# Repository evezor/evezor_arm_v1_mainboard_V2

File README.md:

# evezor_arm_v1_mainboard_V2

This is the second iteration of the mainboard. The first version can be found here: https://github.com/evezor/evezor_arm_v1_mainboard_V1

This board retains the Molex KK connectors for the stepper motors and the gadgeteer ports for expansion. 

This version also incorportates a stepdown voltage converter, a power relay and a pair of USB-A ports inteded for powering a raspberry pi and a screen. 

Source files can be found here: https://github.com/evezor/evezor_arm_v1_mainboard_V2

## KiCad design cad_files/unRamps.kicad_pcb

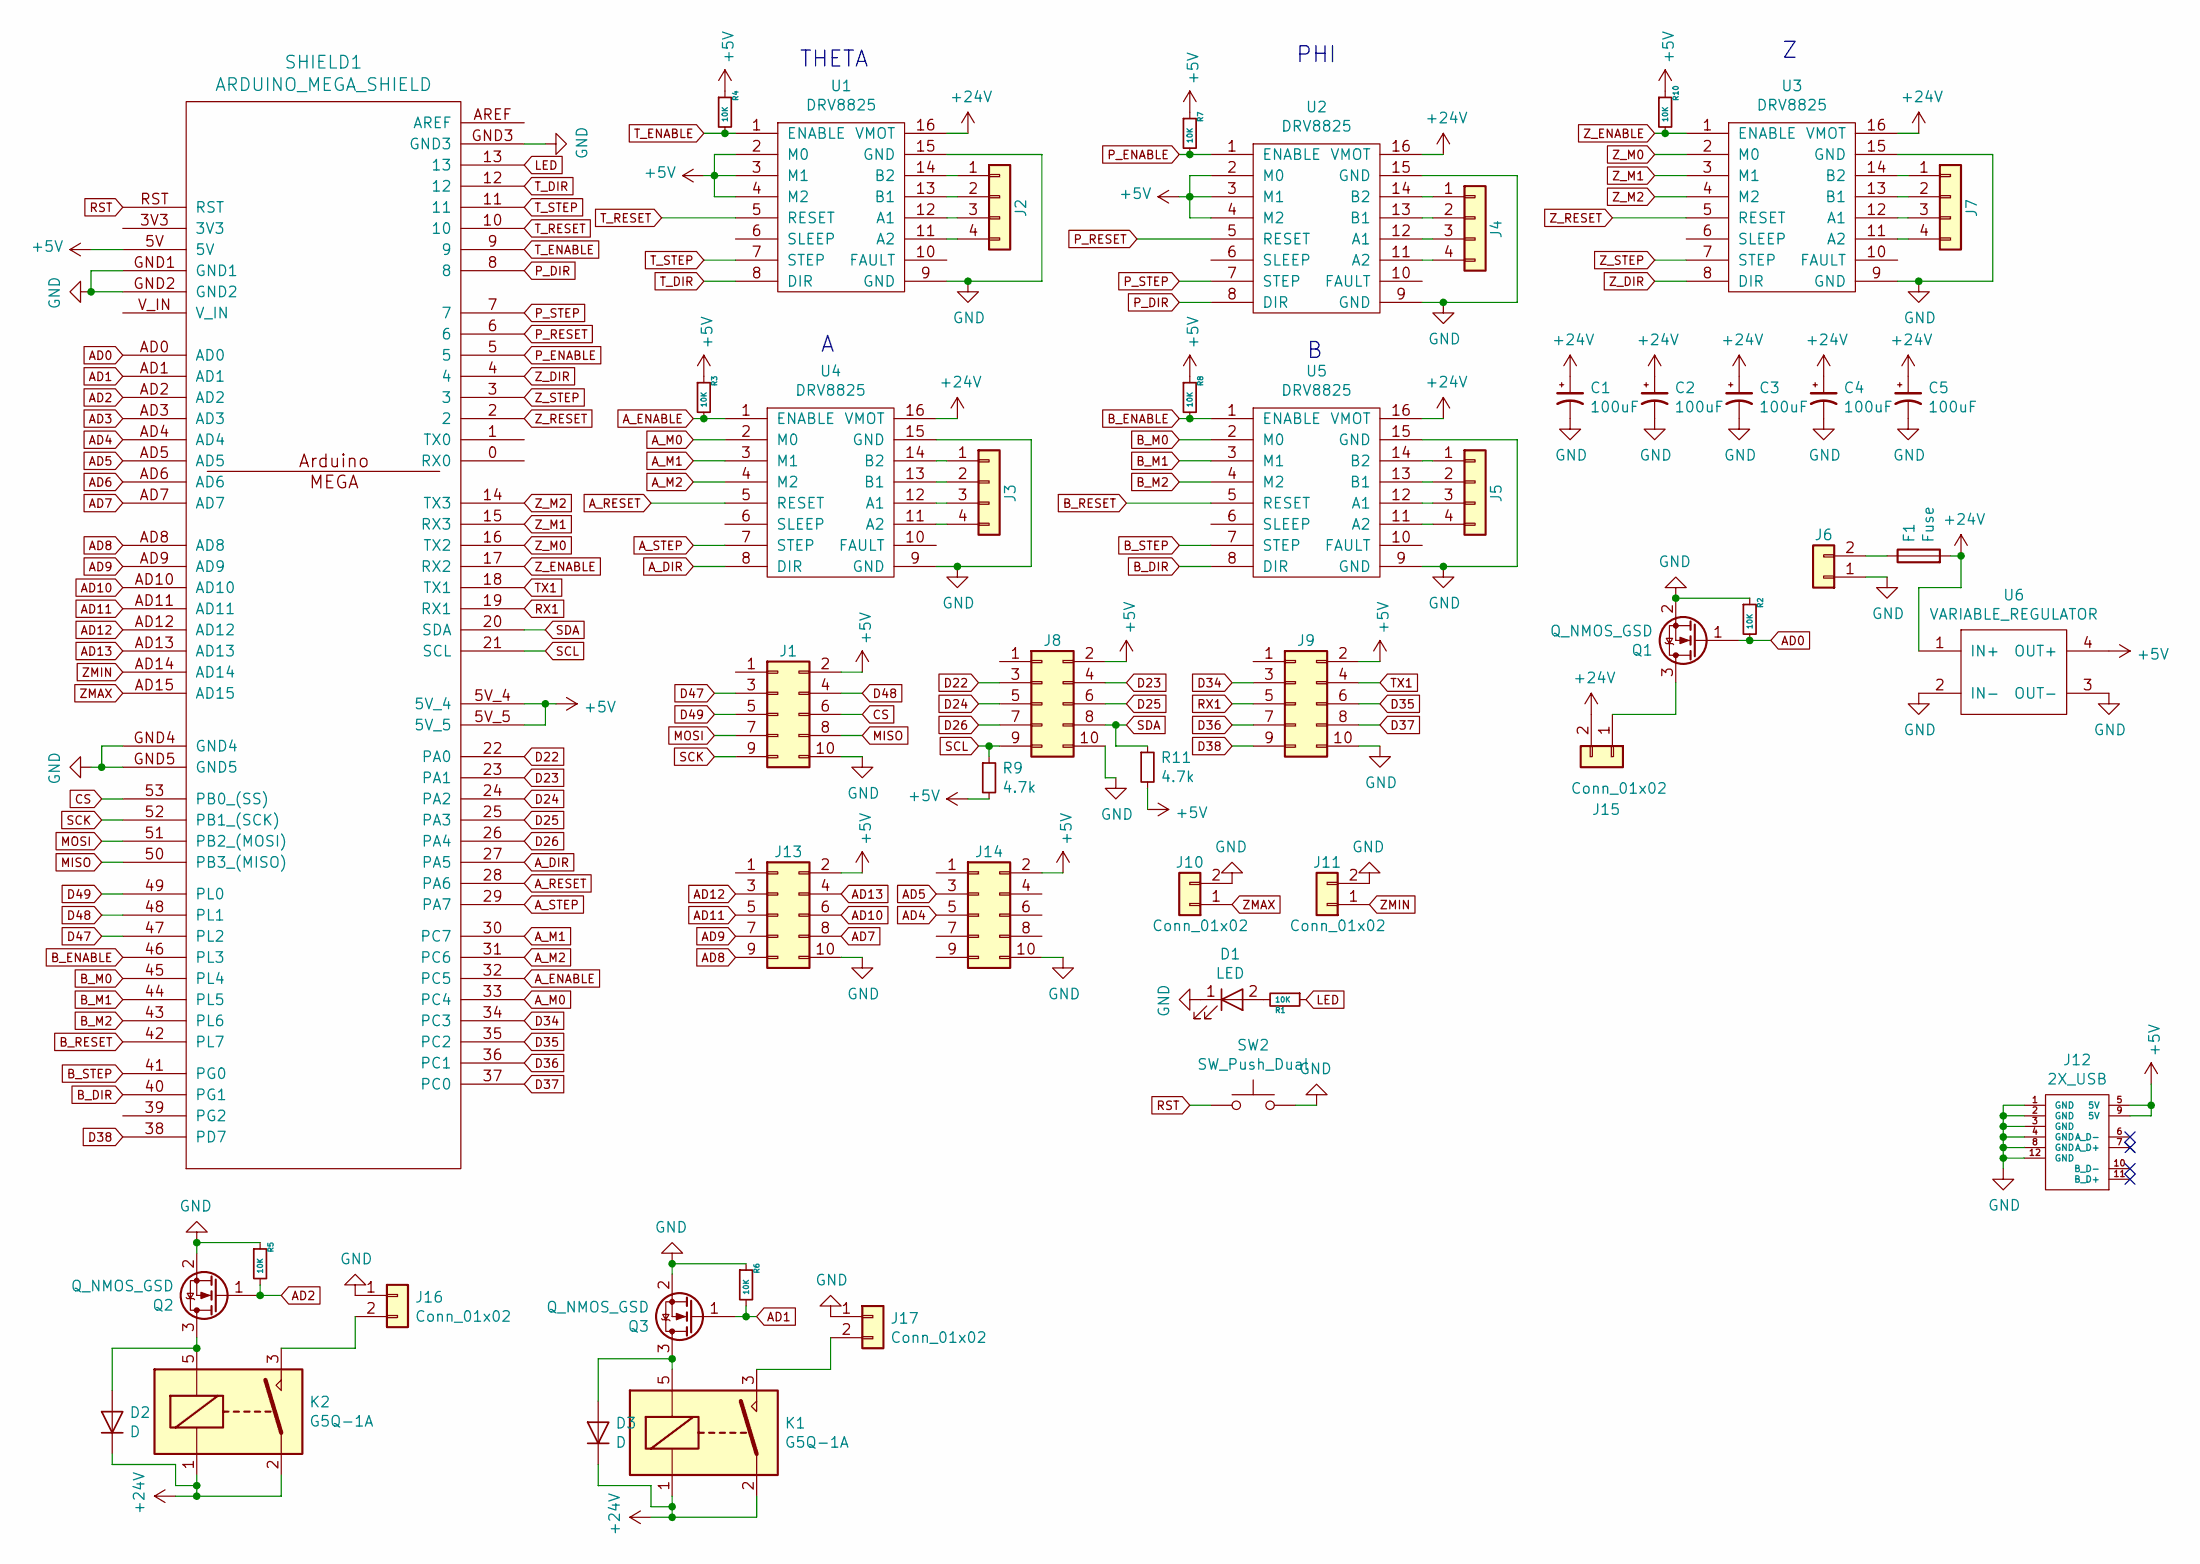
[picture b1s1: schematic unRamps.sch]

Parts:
C1, C2, C3, C4, C5: 100uF; CP_Elec_6.3x5.7
D1: LED; LED_0805
D2, D3: D; D_DO-15_P10.16mm_Horizontal
F1: Fuse; FUSE_BK-6013-ND
J1, J8, J9, J13, J14: Conn_02x05_Odd_Even; 10_PIN_IDC
J2, J3, J4, J5, J7: Conn_01x04; Molex_KK-6410-04_04x2.54mm_Straight
J6, J16, J17: Conn_01x02; CONN_ON_SHORE_2x_15A
J10, J11, J15: Conn_01x02; Pin_Header_Straight_1x02_Pitch2.54mm
J12: 2X_USB; 2X_USB_A
K1, K2: G5Q-1A; Relay_SPDT_OMRON-G5Q
Q1, Q2, Q3: Q_NMOS_GSD; SOT-23
R1, R2, R3, R4, R5, R6, R7, R8, R10: 10K; R_0603
R9, R11: 4.7k; R_0603
SHIELD1: ARDUINO_MEGA_SHIELD; ARDUINO MEGA SHIELD
SW2: SW_Push_Dual; SW_PUSH_6mm
U1, U2, U3, U4, U5: DRV8825
U6: VARIABLE_REGULATOR; LM2596_DC-DC

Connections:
+5V: J1.2, J8.2, J9.2, J12.5 (5V), J12.9 (5V), J13.2, J14.2, R3.1, R4.1, R7.1, R8.1, R9.2, R10.1, R11.2, SHIELD1.5V, SHIELD1.5V_4, SHIELD1.5V_5, U1.2 (M0), U1.3 (M1), U1.4 (M2), U2.2 (M0), U2.3 (M1), U2.4 (M2), U6.4 (OUT+)
+24V: C1.1, C2.1, C3.1, C4.1, C5.1, D2.1 (K), D3.1 (K), F1.2, J15.2, K1.1, K1.2, K2.1, K2.2, U1.16 (VMOT), U2.16 (VMOT), U3.16 (VMOT), U4.16 (VMOT), U5.16 (VMOT), U6.1 (IN+)
AD0: Q1.1 (G), R2.2, SHIELD1.AD0
AD1: Q3.1 (G), R6.2, SHIELD1.AD1
AD2: Q2.1 (G), R5.2, SHIELD1.AD2
AD3: SHIELD1.AD3
AD4: J14.5, SHIELD1.AD4
AD5: J14.3, SHIELD1.AD5
AD6: SHIELD1.AD6
AD7: J13.8, SHIELD1.AD7
AD8: J13.9, SHIELD1.AD8
AD9: J13.7, SHIELD1.AD9
AD10: J13.6, SHIELD1.AD10
AD11: J13.5, SHIELD1.AD11
AD12: J13.3, SHIELD1.AD12
AD13: J13.4, SHIELD1.AD13
A_DIR: SHIELD1.27 (PA5), U4.8 (DIR)
A_ENABLE: R3.2, SHIELD1.32 (PC5), U4.1 (ENABLE)
A_M0: SHIELD1.33 (PC4), U4.2 (M0)
A_M1: SHIELD1.30 (PC7), U4.3 (M1)
A_M2: SHIELD1.31 (PC6), U4.4 (M2)
A_RESET: SHIELD1.28 (PA6), U4.5 (RESET)
A_STEP: SHIELD1.29 (PA7), U4.7 (STEP)
B_DIR: SHIELD1.40 (PG1), U5.8 (DIR)
B_ENABLE: R8.2, SHIELD1.46 (PL3), U5.1 (ENABLE)
B_M0: SHIELD1.45 (PL4), U5.2 (M0)
B_M1: SHIELD1.44 (PL5), U5.3 (M1)
B_M2: SHIELD1.43 (PL6), U5.4 (M2)
B_RESET: SHIELD1.42 (PL7), U5.5 (RESET)
B_STEP: SHIELD1.41 (PG0), U5.7 (STEP)
CS: J1.6, SHIELD1.53 (PB0_(SS))
D22: J8.3, SHIELD1.22 (PA0)
D23: J8.4, SHIELD1.23 (PA1)
D24: J8.5, SHIELD1.24 (PA2)
D25: J8.6, SHIELD1.25 (PA3)
D26: J8.7, SHIELD1.26 (PA4)
D34: J9.3, SHIELD1.34 (PC3)
D35: J9.6, SHIELD1.35 (PC2)
D36: J9.7, SHIELD1.36 (PC1)
D37: J9.8, SHIELD1.37 (PC0)
D38: J9.9, SHIELD1.38 (PD7)
D47: J1.3, SHIELD1.47 (PL2)
D48: J1.4, SHIELD1.48 (PL1)
D49: J1.5, SHIELD1.49 (PL0)
GND: C1.2, C2.2, C3.2, C4.2, C5.2, D1.1 (K), J1.10, J6.1, J8.10, J9.10, J10.2, J11.2, J12.1 (GND), J12.2 (GND), J12.3 (GND), J12.4 (GND), J12.8 (GND), J12.12 (GND), J13.10, J14.10, J16.1, J17.1, Q1.2 (S), Q2.2 (S), Q3.2 (S), R2.1, R5.1, R6.1, SHIELD1.GND1, SHIELD1.GND2, SHIELD1.GND3, SHIELD1.GND4, SHIELD1.GND5, SW2.2, U1.9 (GND), U1.15 (GND), U2.9 (GND), U2.15 (GND), U3.9 (GND), U3.15 (GND), U4.9 (GND), U4.15 (GND), U5.9 (GND), U5.15 (GND), U6.2 (IN-), U6.3 (OUT-)
LED: R1.1, SHIELD1.13
MISO: J1.8, SHIELD1.50 (PB3_(MISO))
MOSI: J1.7, SHIELD1.51 (PB2_(MOSI))
unnamed: D1.2 (A), R1.2
unnamed: D2.2 (A), K2.5, Q2.3 (D)
unnamed: D3.2 (A), K1.5, Q3.3 (D)
unnamed: F1.1, J6.2
unnamed: J2.1, U1.14 (B2)
unnamed: J2.2, U1.13 (B1)
unnamed: J2.3, U1.12 (A1)
unnamed: J2.4, U1.11 (A2)
unnamed: J3.1, U4.14 (B2)
unnamed: J3.2, U4.13 (B1)
unnamed: J3.3, U4.12 (A1)
unnamed: J3.4, U4.11 (A2)
unnamed: J4.1, U2.14 (B2)
unnamed: J4.2, U2.13 (B1)
unnamed: J4.3, U2.12 (A1)
unnamed: J4.4, U2.11 (A2)
unnamed: J5.1, U5.14 (B2)
unnamed: J5.2, U5.13 (B1)
unnamed: J5.3, U5.12 (A1)
unnamed: J5.4, U5.11 (A2)
unnamed: J7.1, U3.14 (B2)
unnamed: J7.2, U3.13 (B1)
unnamed: J7.3, U3.12 (A1)
unnamed: J7.4, U3.11 (A2)
unnamed: J15.1, Q1.3 (D)
unnamed: J16.2, K2.3
unnamed: J17.2, K1.3
P_DIR: SHIELD1.8, U2.8 (DIR)
P_ENABLE: R7.2, SHIELD1.5, U2.1 (ENABLE)
P_RESET: SHIELD1.6, U2.5 (RESET)
P_STEP: SHIELD1.7, U2.7 (STEP)
RST: SHIELD1.RST, SW2.1
RX1: J9.5, SHIELD1.19 (RX1)
SCK: J1.9, SHIELD1.52 (PB1_(SCK))
SCL: J8.9, R9.1, SHIELD1.21 (SCL)
SDA: J8.8, R11.1, SHIELD1.20 (SDA)
TX1: J9.4, SHIELD1.18 (TX1)
T_DIR: SHIELD1.12, U1.8 (DIR)
T_ENABLE: R4.2, SHIELD1.9, U1.1 (ENABLE)
T_RESET: SHIELD1.10, U1.5 (RESET)
T_STEP: SHIELD1.11, U1.7 (STEP)
ZMAX: J10.1, SHIELD1.AD15
ZMIN: J11.1, SHIELD1.AD14
Z_DIR: SHIELD1.4, U3.8 (DIR)
Z_ENABLE: R10.2, SHIELD1.17 (RX2), U3.1 (ENABLE)
Z_M0: SHIELD1.16 (TX2), U3.2 (M0)
Z_M1: SHIELD1.15 (RX3), U3.3 (M1)
Z_M2: SHIELD1.14 (TX3), U3.4 (M2)
Z_RESET: SHIELD1.2, U3.5 (RESET)
Z_STEP: SHIELD1.3, U3.7 (STEP)

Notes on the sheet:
THETA
PHI

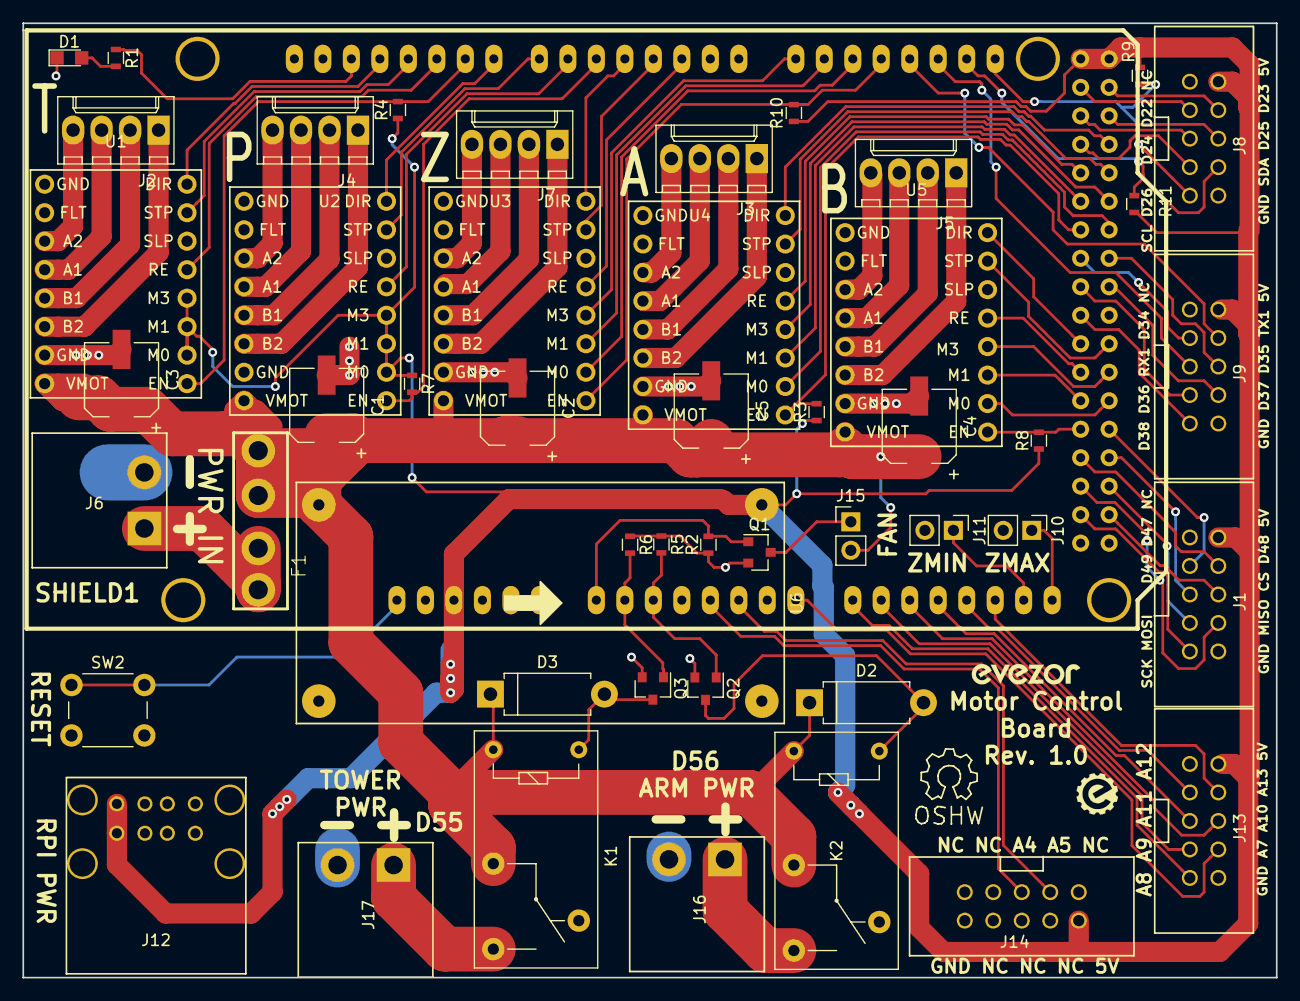
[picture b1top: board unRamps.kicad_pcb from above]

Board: 2 copper layers, 111.8 x 85.1 mm, 50 parts (0 on the bottom side), 96 nets.

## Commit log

2023-10-06 init
